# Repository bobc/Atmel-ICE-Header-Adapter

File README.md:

# Atmel-ICE-Header-Adapter
Atmel ICE header adapter from https://atoomnet.net/atmel-ice-header-adapter

This is a KiCad version of Atmel ICE header adapter by marc. See https://atoomnet.net/atmel-ice-header-adapter for more info.

# Version 1
## Schematic

## PCB

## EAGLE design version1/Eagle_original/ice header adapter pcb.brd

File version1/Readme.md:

# Atmel Ice Header Adapter 

This is the "version 1" PCB. I made a few minor changes, but the board is functionally equivalent to the original Eagle PCB.

# Gerbers

Gerbers are in the gerbers folder. There is a zip file which I use with Itead PCB service. The "gvp" file is a gerbv project file. https://sourceforge.net/projects/gerbv/

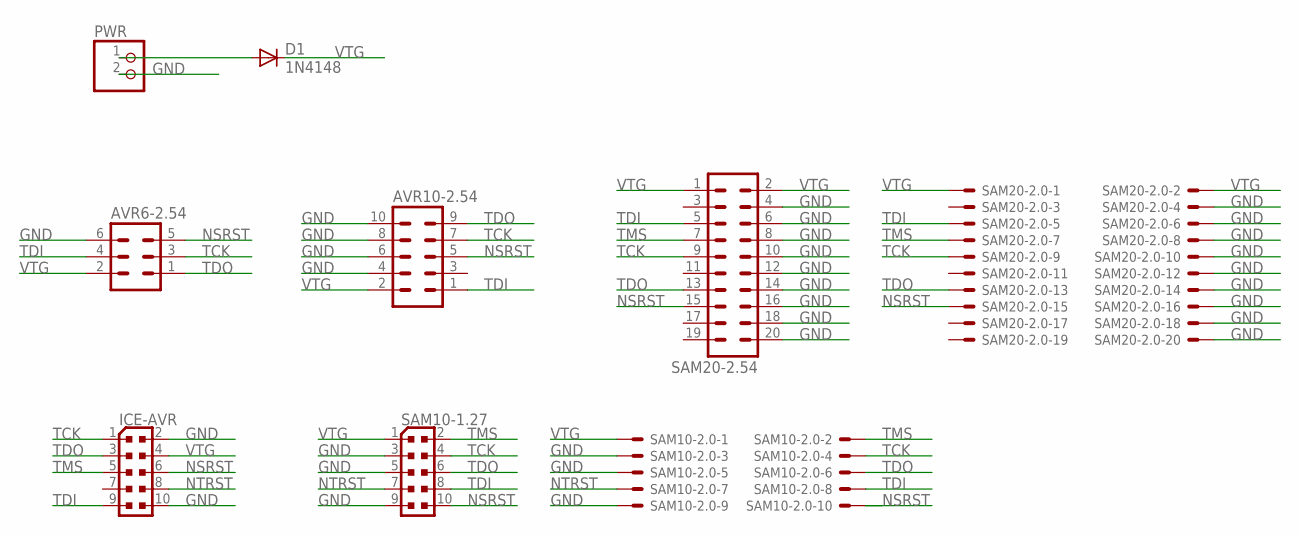
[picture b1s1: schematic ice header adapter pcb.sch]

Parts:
AVR6-2.54: ML6
AVR10-2.54: ML10
D1: 1N4148; DO35-7
ICE-AVR: PINHEAD_PINHD-2X5PASSO127; PINHEAD_2X05_127
PWR: PINHD-1X2/90; 1X02/90
SAM10-1.27: PINHEAD_PINHD-2X5PASSO127; PINHEAD_2X05_127
SAM10-2.0: 87758-1016
SAM20-2.0: 87758-2016
SAM20-2.54: ML20

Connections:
GND: AVR6-2.54.6, AVR10-2.54.4, AVR10-2.54.6, AVR10-2.54.8, AVR10-2.54.10, ICE-AVR.2, ICE-AVR.10, PWR.2, SAM10-1.27.3, SAM10-1.27.5, SAM10-1.27.9, SAM10-2.0.3, SAM10-2.0.5, SAM10-2.0.9, SAM20-2.0.4, SAM20-2.0.6, SAM20-2.0.8, SAM20-2.0.10, SAM20-2.0.12, SAM20-2.0.14, SAM20-2.0.16, SAM20-2.0.18, SAM20-2.0.20, SAM20-2.54.4, SAM20-2.54.6, SAM20-2.54.8, SAM20-2.54.10, SAM20-2.54.12, SAM20-2.54.14, SAM20-2.54.16, SAM20-2.54.18, SAM20-2.54.20
unnamed: D1.A, PWR.1
NSRST: AVR6-2.54.5, AVR10-2.54.5, ICE-AVR.6, SAM10-1.27.10, SAM10-2.0.10, SAM20-2.0.15, SAM20-2.54.15
NTRST: ICE-AVR.8, SAM10-1.27.7, SAM10-2.0.7
TCK: AVR6-2.54.3, AVR10-2.54.7, ICE-AVR.1, SAM10-1.27.4, SAM10-2.0.4, SAM20-2.0.9, SAM20-2.54.9
TDI: AVR6-2.54.4, AVR10-2.54.1, ICE-AVR.9, SAM10-1.27.8, SAM10-2.0.8, SAM20-2.0.5, SAM20-2.54.5
TDO: AVR6-2.54.1, AVR10-2.54.9, ICE-AVR.3, SAM10-1.27.6, SAM10-2.0.6, SAM20-2.0.13, SAM20-2.54.13
TMS: ICE-AVR.5, SAM10-1.27.2, SAM10-2.0.2, SAM20-2.0.7, SAM20-2.54.7
VTG: AVR6-2.54.2, AVR10-2.54.2, D1.C, ICE-AVR.4, SAM10-1.27.1, SAM10-2.0.1, SAM20-2.0.1, SAM20-2.0.2, SAM20-2.54.1, SAM20-2.54.2

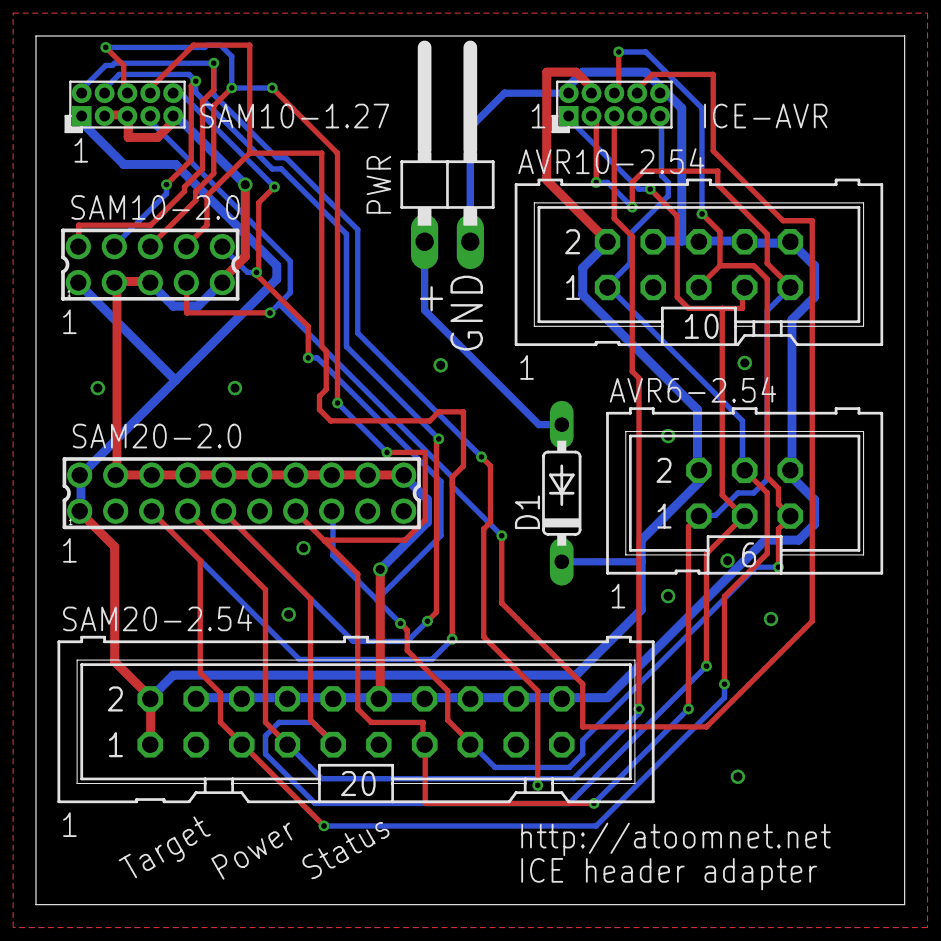
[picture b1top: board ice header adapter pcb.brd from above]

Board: 2 copper layers, 48.3 x 48.3 mm, 9 parts (0 on the bottom side), 9 nets.

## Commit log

2017-04-30 Update gitignore
